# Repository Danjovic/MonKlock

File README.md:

# MonKlock

Cistercian Monk's cypher digital clock.
Resources
---------

- Project page at [hackaday](www.hackaday.com)

Features
--------

- Large (4 inch) 5x7 LED matrix
- Arduino Nano based
- DS3231 high precision RTC
- HH:MM or Decimal time
- Time, Day, Month and Year
- Single sided PCB

Contribute or Support
---------------------

If you are having issues, please email the athor [danjovic@hotmail.com](mailto:dnajovic@hotmail.com).

License
-------

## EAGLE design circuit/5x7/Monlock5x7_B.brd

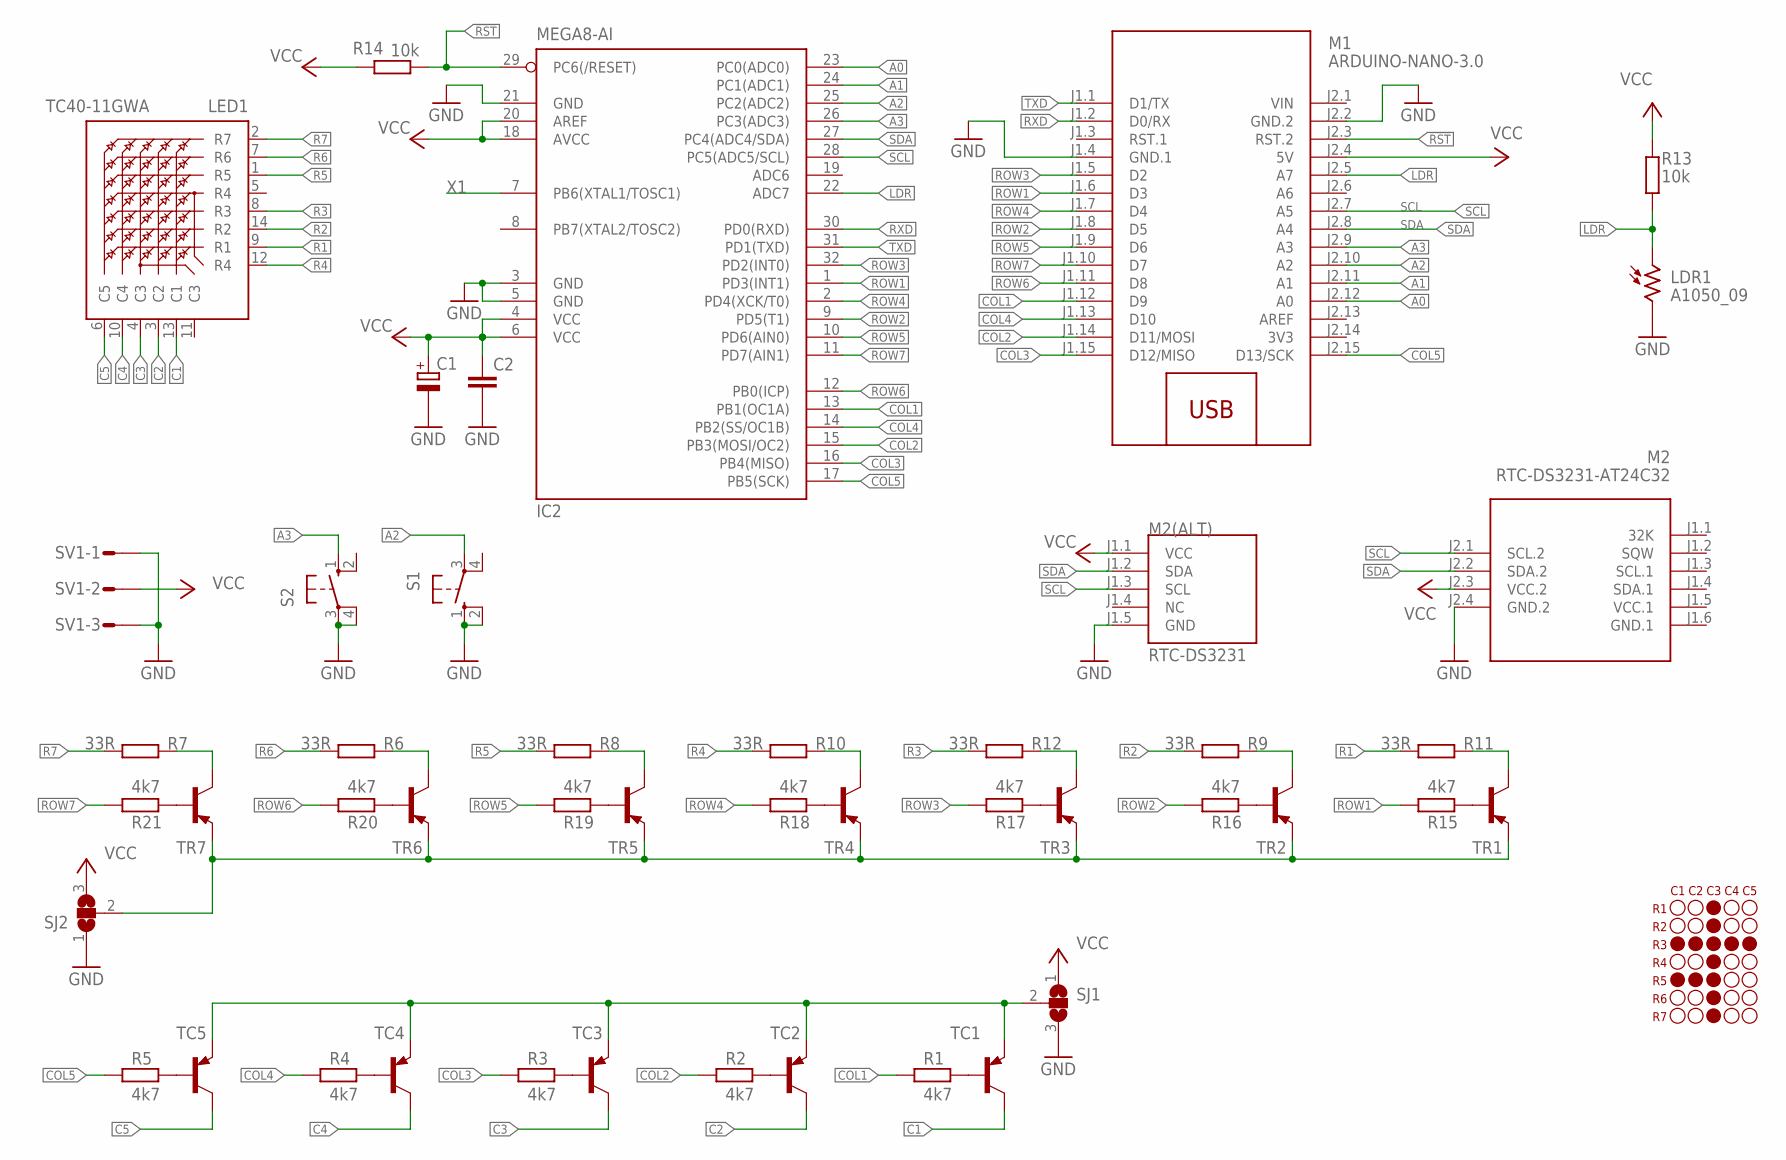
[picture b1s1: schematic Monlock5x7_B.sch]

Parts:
C1: CPOL-EU153CLV-0605; 153CLV-0605
C2: C-EUC0805K; C0805K
IC2: MEGA8-AI; TQFP32-08
LDR1: A1050_09; T0-46-A10XX
LED1: TC40-11GWA
M1: ARDUINO-NANO-3.0
M2: RTC-DS3231-AT24C32
M2(ALT): RTC-DS3231; RTC-DS3231_SMALL
R1, R2, R3, R4, R5, R15, R16, R17, R18, R19, R20, R21: 4k7; 0204/7
R6, R7, R8, R9, R10, R11, R12: 33R; 0204/7
R13: 10k; 0204/7
R14: 10k; M0805
S1, S2: 40-XX; B3F-40XX
SJ1, SJ2: SJ2W; SJ_2
SV1: S03P
TC1, TC2, TC3, TC4, TC5: BC327-PNP-TO92-EBC; TO92-EBC
TR1, TR2, TR3, TR4, TR5, TR6, TR7: BC327-PNP-TO92-EBC; TO92-EBC

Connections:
3V3: M1.J2.14 (3V3)
!RST: IC2.29 (PC6(/RESET)), M1.J2.3 (RST.2), R14.1
A0: IC2.23 (PC0(ADC0)), M1.J2.12 (A0)
A1: IC2.24 (PC1(ADC1)), M1.J2.11 (A1)
A2: IC2.25 (PC2(ADC2)), M1.J2.10 (A2), S1.3
A3: IC2.26 (PC3(ADC3)), M1.J2.9 (A3), S2.1 (S)
C1: LED1.13 (C1), TC1.C
C2: LED1.3 (C2), TC2.C
C3: LED1.4 (C3), TC3.C
C4: LED1.10 (C4), TC4.C
C5: LED1.6 (C5), TC5.C
CC1: R1.2, TC1.B
CC2: R2.2, TC2.B
CC3: R3.2, TC3.B
CC4: R4.2, TC4.B
CC5: R5.2, TC5.B
CC6: R15.2, TR1.B
COL1: IC2.13 (PB1(OC1A)), M1.J1.12 (D9), R1.1
COL2: IC2.15 (PB3(MOSI/OC2)), M1.J1.14 (D11/MOSI), R2.1
COL3: IC2.16 (PB4(MISO)), M1.J1.15 (D12/MISO), R3.1
COL4: IC2.14 (PB2(SS/OC1B)), M1.J1.13 (D10), R4.1
COL5: IC2.17 (PB5(SCK)), M1.J2.15 (D13/SCK), R5.1
GND: C1.-, C2.2, IC2.3 (GND), IC2.5 (GND), IC2.21 (GND), LDR1.2, M1.J1.4 (GND.1), M1.J2.2 (GND.2), M2.J2.4 (GND.2), M2(ALT).J1.5 (GND), S1.1 (S), S1.2 (S1), S2.3, S2.4 (P1), SJ1.3, SJ2.1, SV1.1, SV1.3
GND.1: M2.J1.6 (GND.1)
LDR: IC2.22 (ADC7), LDR1.1, M1.J2.5 (A7), R13.1
unnamed: SJ1.2, TC1.E, TC2.E, TC3.E, TC4.E, TC5.E
unnamed: SJ2.2, TR1.E, TR2.E, TR3.E, TR4.E, TR5.E, TR6.E, TR7.E
unnamed: R16.2, TR2.B
unnamed: R17.2, TR3.B
unnamed: R18.2, TR4.B
unnamed: R19.2, TR5.B
unnamed: R20.2, TR6.B
unnamed: R21.2, TR7.B
unnamed: R7.2, TR7.C
unnamed: R6.2, TR6.C
unnamed: R8.2, TR5.C
unnamed: R10.2, TR4.C
unnamed: R12.2, TR3.C
unnamed: R9.2, TR2.C
unnamed: R11.2, TR1.C
R1: LED1.9 (R1), R11.1
R2: LED1.14 (R2), R9.1
R3: LED1.8 (R3), R12.1
R4: LED1.12 (R4), R10.1
R5: LED1.1 (R5), R8.1
R6: LED1.7 (R6), R6.1
R7: LED1.2 (R7), R7.1
ROW1: IC2.1 (PD3(INT1)), M1.J1.6 (D3), R15.1
ROW2: IC2.9 (PD5(T1)), M1.J1.8 (D5), R16.1
ROW3: IC2.32 (PD2(INT0)), M1.J1.5 (D2), R17.1
ROW4: IC2.2 (PD4(XCK/T0)), M1.J1.7 (D4), R18.1
ROW5: IC2.10 (PD6(AIN0)), M1.J1.9 (D6), R19.1
ROW6: IC2.12 (PB0(ICP)), M1.J1.11 (D8), R20.1
ROW7: IC2.11 (PD7(AIN1)), M1.J1.10 (D7), R21.1
RXD: IC2.30 (PD0(RXD)), M1.J1.2 (D0/RX)
SCL: IC2.28 (PC5(ADC5/SCL)), M1.J2.7 (A5), M2.J2.1 (SCL.2), M2(ALT).J1.3 (SCL)
SDA: IC2.27 (PC4(ADC4/SDA)), M1.J2.8 (A4), M2.J2.2 (SDA.2), M2(ALT).J1.2 (SDA)
TXD: IC2.31 (PD1(TXD)), M1.J1.1 (D1/TX)
VCC: C1.+, C2.1, IC2.4 (VCC), IC2.6 (VCC), IC2.18 (AVCC), IC2.20 (AREF), M1.J2.4 (5V), M2.J2.3 (VCC.2), M2(ALT).J1.1 (VCC), R13.2, R14.2, SJ1.1, SJ2.3, SV1.2
VCC.1: M2.J1.5 (VCC.1)
VIN: M1.J2.1 (VIN)
X1: IC2.7 (PB6(XTAL1/TOSC1))

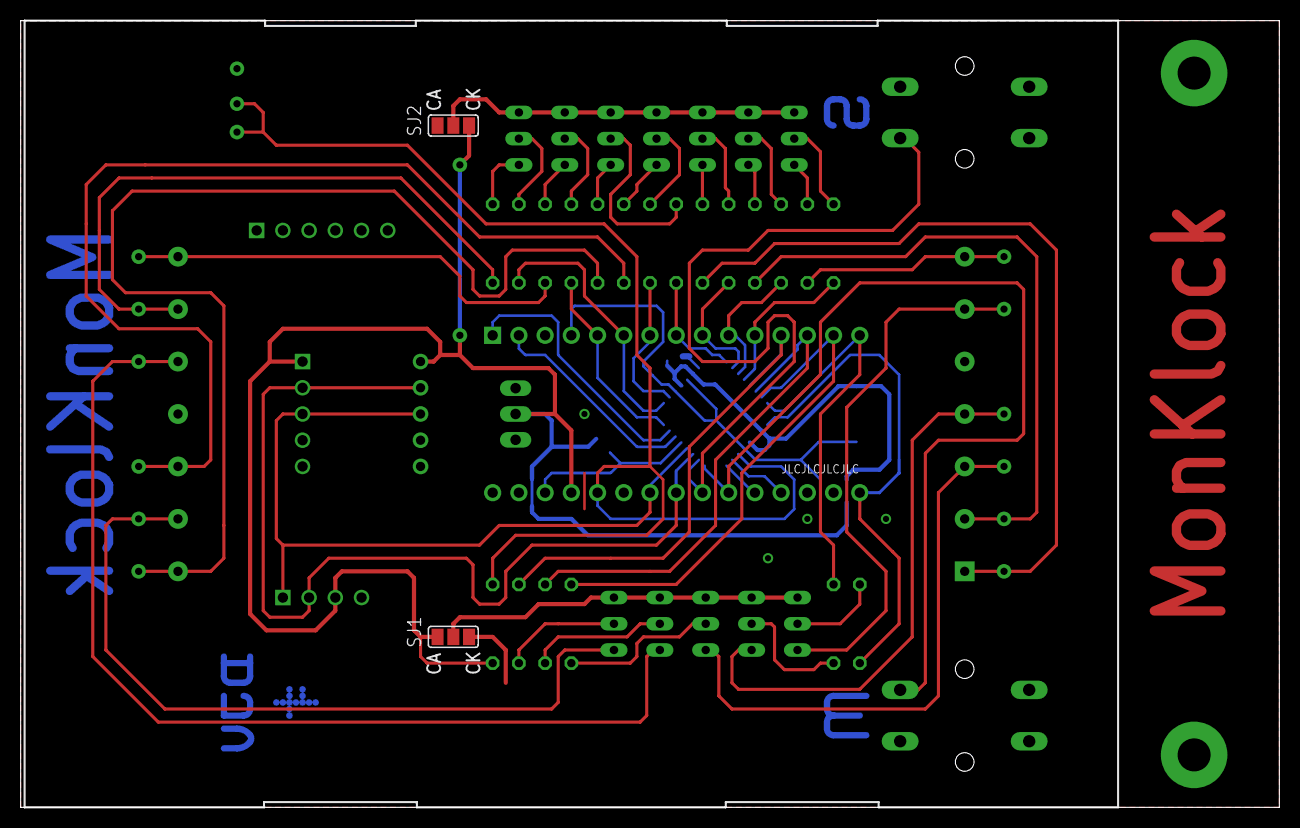
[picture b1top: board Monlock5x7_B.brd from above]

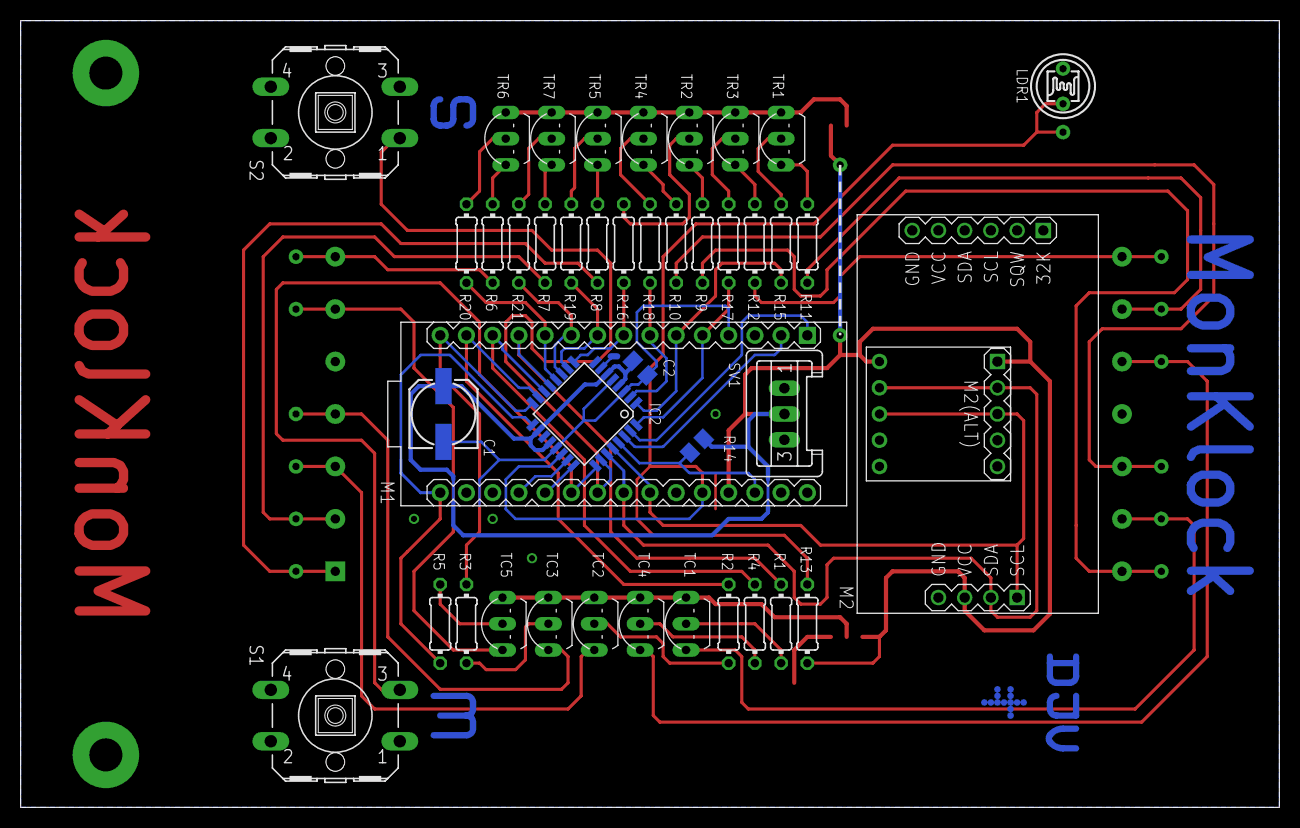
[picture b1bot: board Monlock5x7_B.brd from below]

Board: 2 copper layers, 121.9 x 76.2 mm, 46 parts (43 on the bottom side), 57 nets.

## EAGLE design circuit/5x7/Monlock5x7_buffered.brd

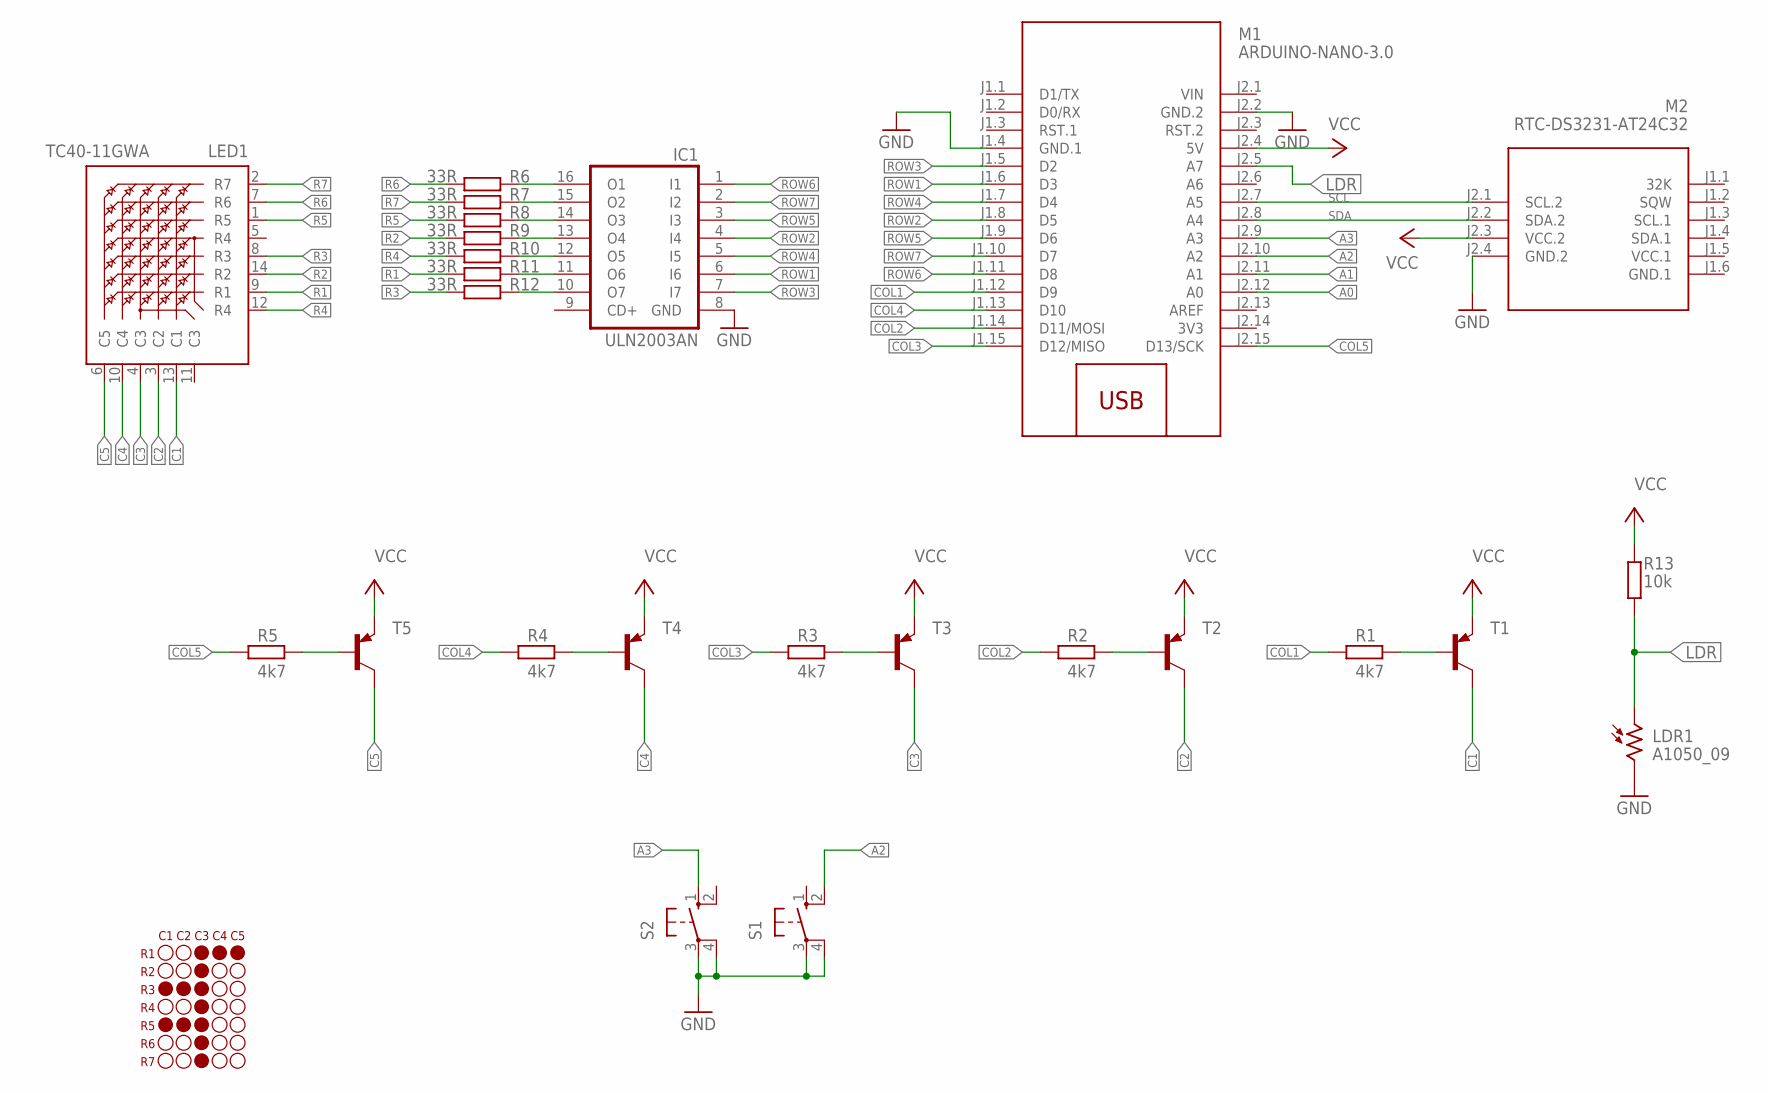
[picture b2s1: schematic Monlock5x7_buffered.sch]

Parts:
IC1: ULN2003AN; DIL16
LDR1: A1050_09; T0-46-A10XX
LED1: TC40-11GWA
M1: ARDUINO-NANO-3.0
M2: RTC-DS3231-AT24C32
R1, R2, R3, R4, R5: 4k7; 0204/7
R6, R7, R8, R9, R10, R11, R12: 33R; 0204/7
R13: 10k; 0204/7
S1, S2: 40-XX; B3F-40XX
T1, T2, T3, T4, T5: BC327-PNP-TO92-EBC; TO92-EBC

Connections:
3V3: M1.J2.14 (3V3)
A0: M1.J2.12 (A0)
A1: M1.J2.11 (A1)
A2: M1.J2.10 (A2), S1.2 (S1)
A3: M1.J2.9 (A3), S2.1 (S)
C1: LED1.13 (C1), T1.C
C2: LED1.3 (C2), T2.C
C3: LED1.4 (C3), T3.C
C4: LED1.10 (C4), T4.C
C5: LED1.6 (C5), T5.C
CC1: R1.2, T1.B
CC2: R2.2, T2.B
CC3: R3.2, T3.B
CC4: R4.2, T4.B
CC5: R5.2, T5.B
COL1: M1.J1.12 (D9), R1.1
COL2: M1.J1.14 (D11/MOSI), R2.1
COL3: M1.J1.15 (D12/MISO), R3.1
COL4: M1.J1.13 (D10), R4.1
COL5: M1.J2.15 (D13/SCK), R5.1
GND: IC1.8 (GND), LDR1.2, M1.J1.4 (GND.1), M1.J2.2 (GND.2), M2.J1.6 (GND.1), M2.J2.4 (GND.2), S1.3, S1.4 (P1), S2.3, S2.4 (P1)
LDR: LDR1.1, M1.J2.5 (A7), R13.1
unnamed: IC1.16 (O1), R6.2
unnamed: IC1.15 (O2), R7.2
unnamed: IC1.14 (O3), R8.2
unnamed: IC1.13 (O4), R9.2
unnamed: IC1.12 (O5), R10.2
unnamed: IC1.11 (O6), R11.2
unnamed: IC1.10 (O7), R12.2
R1: LED1.9 (R1), R11.1
R2: LED1.14 (R2), R9.1
R3: LED1.8 (R3), R12.1
R4: LED1.12 (R4), R10.1
R5: LED1.1 (R5), R8.1
R6: LED1.7 (R6), R6.1
R7: LED1.2 (R7), R7.1
ROW1: IC1.6 (I6), M1.J1.6 (D3)
ROW2: IC1.4 (I4), M1.J1.8 (D5)
ROW3: IC1.7 (I7), M1.J1.5 (D2)
ROW4: IC1.5 (I5), M1.J1.7 (D4)
ROW5: IC1.3 (I3), M1.J1.9 (D6)
ROW6: IC1.1 (I1), M1.J1.11 (D8)
ROW7: IC1.2 (I2), M1.J1.10 (D7)
SCL: M1.J2.7 (A5), M2.J2.1 (SCL.2)
SDA: M1.J2.8 (A4), M2.J2.2 (SDA.2)
VCC: M1.J2.4 (5V), M2.J2.3 (VCC.2), R13.2, T1.E, T2.E, T3.E, T4.E, T5.E
VCC.1: M2.J1.5 (VCC.1)
VIN: M1.J2.1 (VIN)

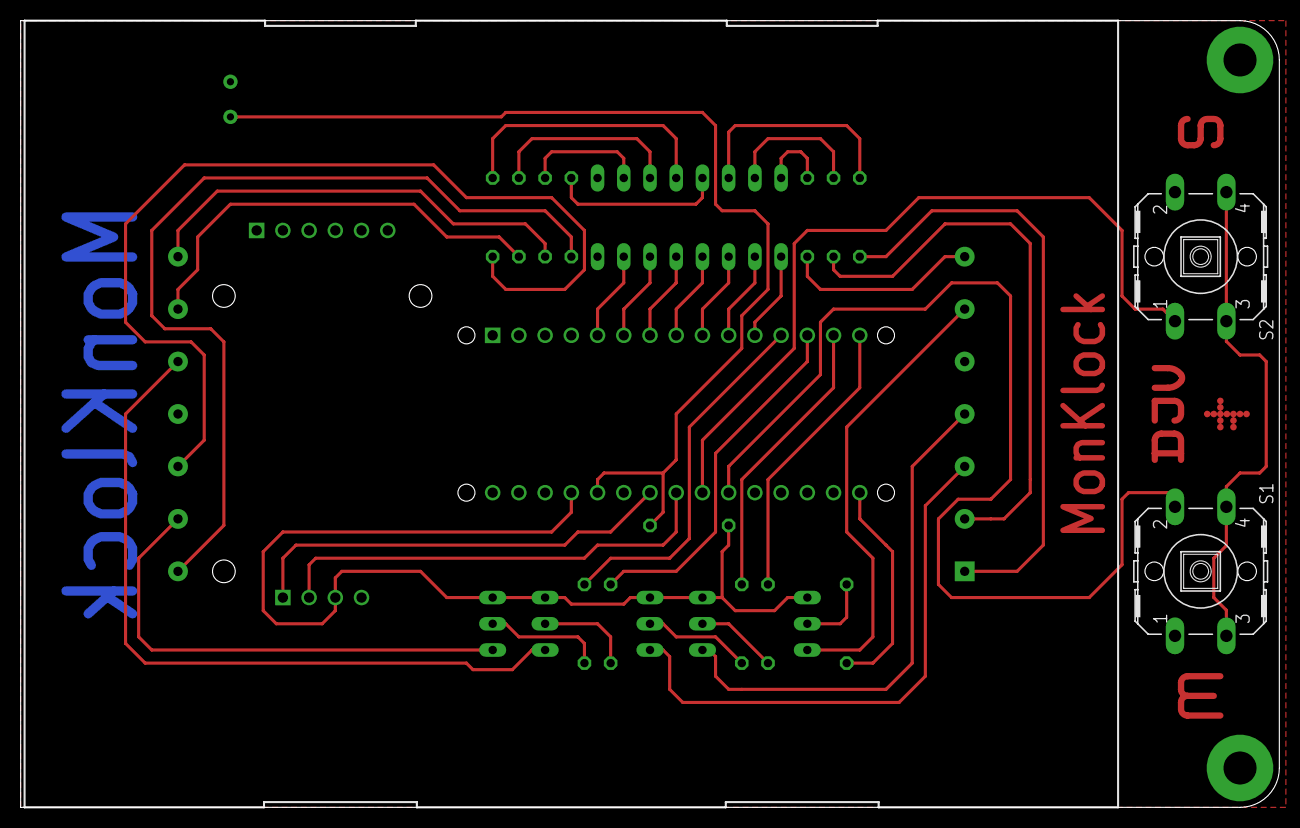
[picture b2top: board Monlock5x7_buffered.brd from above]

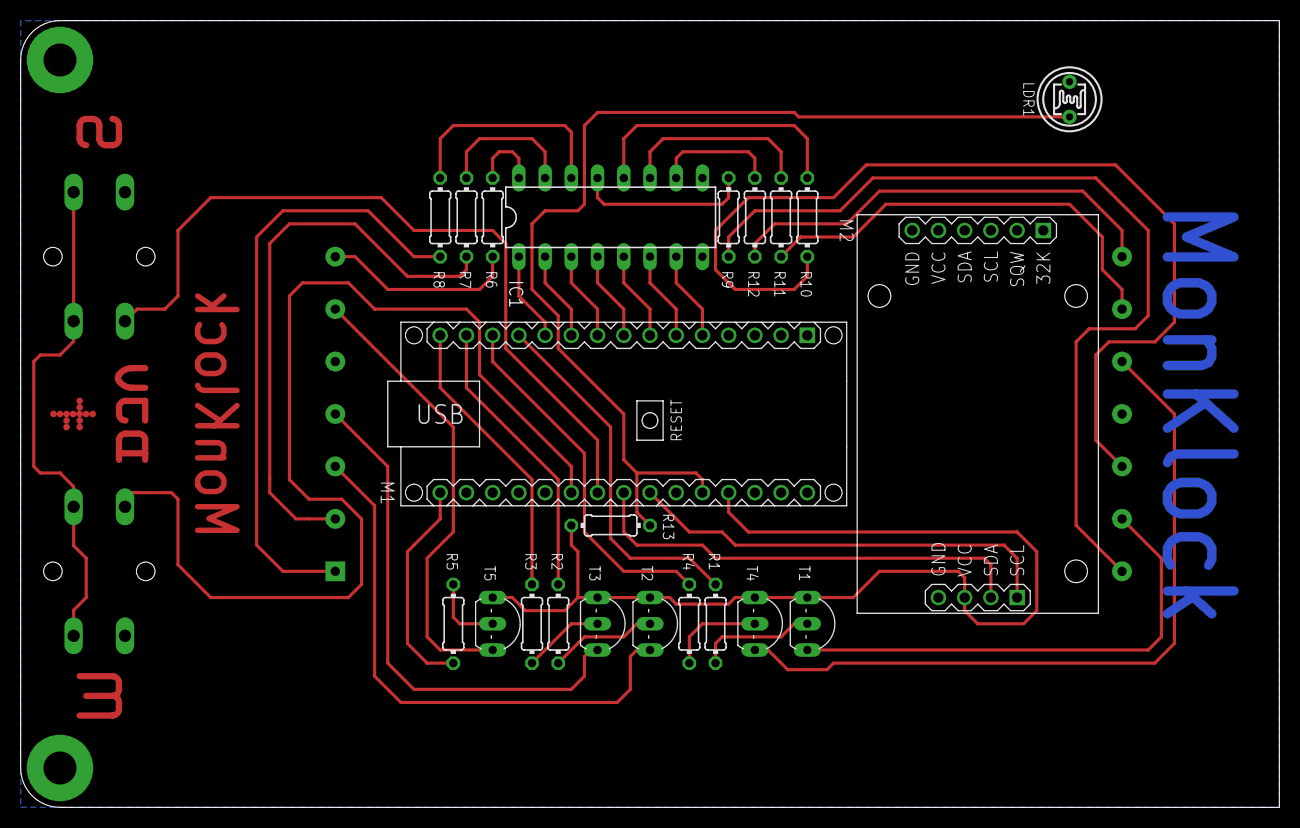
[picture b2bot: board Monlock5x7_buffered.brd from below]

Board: 2 copper layers, 121.9 x 76.2 mm, 25 parts (22 on the bottom side), 43 nets.

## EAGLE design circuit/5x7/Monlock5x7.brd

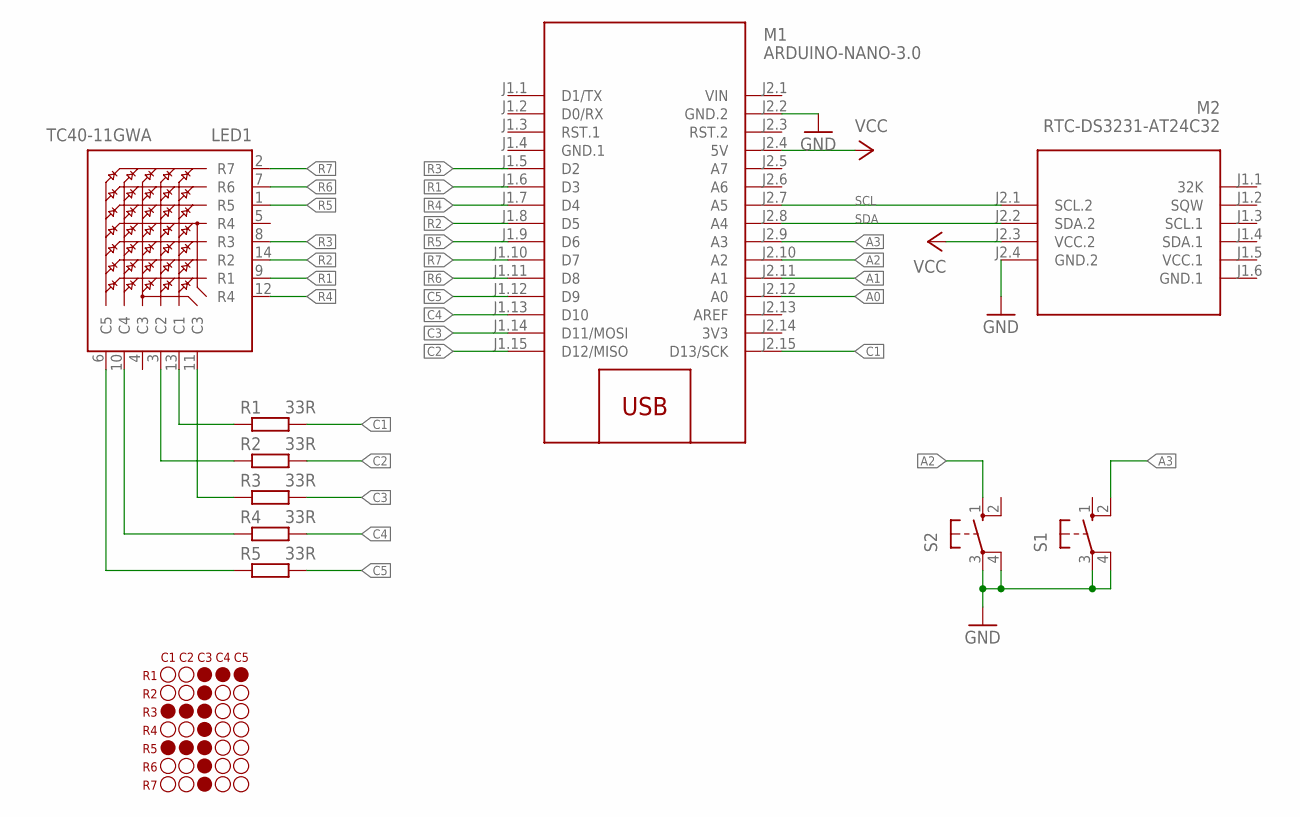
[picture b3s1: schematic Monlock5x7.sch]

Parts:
LED1: TC40-11GWA
M1: ARDUINO-NANO-3.0
M2: RTC-DS3231-AT24C32
R1, R2, R3, R4, R5: 33R; 0204/7
S1, S2: 40-XX; B3F-40XX

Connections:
3V3: M1.J2.14 (3V3)
A0: M1.J2.12 (A0)
A1: M1.J2.11 (A1)
A2: M1.J2.10 (A2), S2.1 (S)
A3: M1.J2.9 (A3), S1.2 (S1)
C1: M1.J2.15 (D13/SCK), R1.1
C2: M1.J1.15 (D12/MISO), R2.1
C3: M1.J1.14 (D11/MOSI), R3.1
C4: M1.J1.13 (D10), R4.1
C5: M1.J1.12 (D9), R5.1
CC1: LED1.13 (C1), R1.2
CC2: LED1.3 (C2), R2.2
CC3: LED1.11 (C3), R3.2
CC4: LED1.10 (C4), R4.2
CC5: LED1.6 (C5), R5.2
GND: M1.J1.4 (GND.1), M1.J2.2 (GND.2), M2.J1.6 (GND.1), M2.J2.4 (GND.2), S1.3, S1.4 (P1), S2.3, S2.4 (P1)
R1: LED1.9 (R1), M1.J1.6 (D3)
R2: LED1.14 (R2), M1.J1.8 (D5)
R3: LED1.8 (R3), M1.J1.5 (D2)
R4: LED1.12 (R4), M1.J1.7 (D4)
R5: LED1.1 (R5), M1.J1.9 (D6)
R6: LED1.7 (R6), M1.J1.11 (D8)
R7: LED1.2 (R7), M1.J1.10 (D7)
SCL: M1.J2.7 (A5), M2.J2.1 (SCL.2)
SDA: M1.J2.8 (A4), M2.J2.2 (SDA.2)
VCC: M1.J2.4 (5V), M2.J2.3 (VCC.2)
VCC.1: M2.J1.5 (VCC.1)
VIN: M1.J2.1 (VIN)

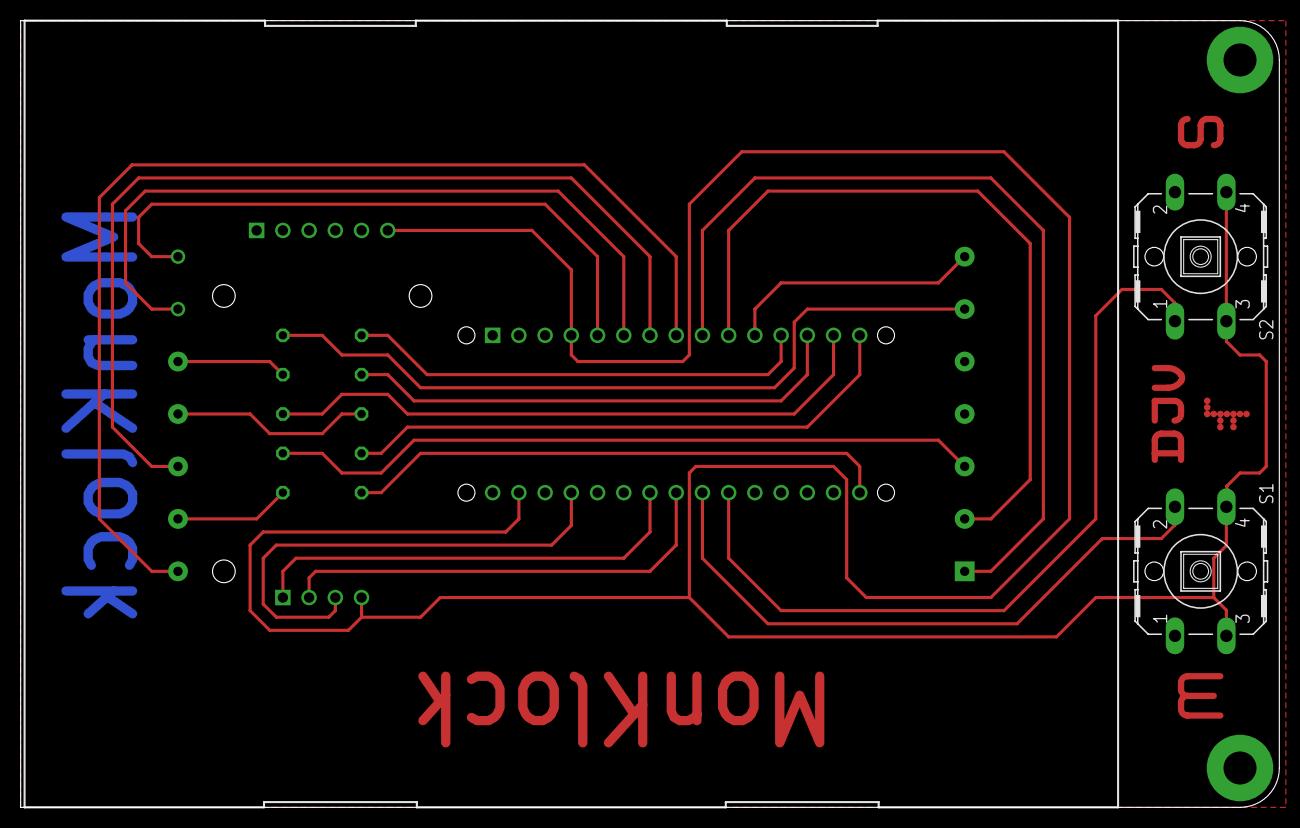
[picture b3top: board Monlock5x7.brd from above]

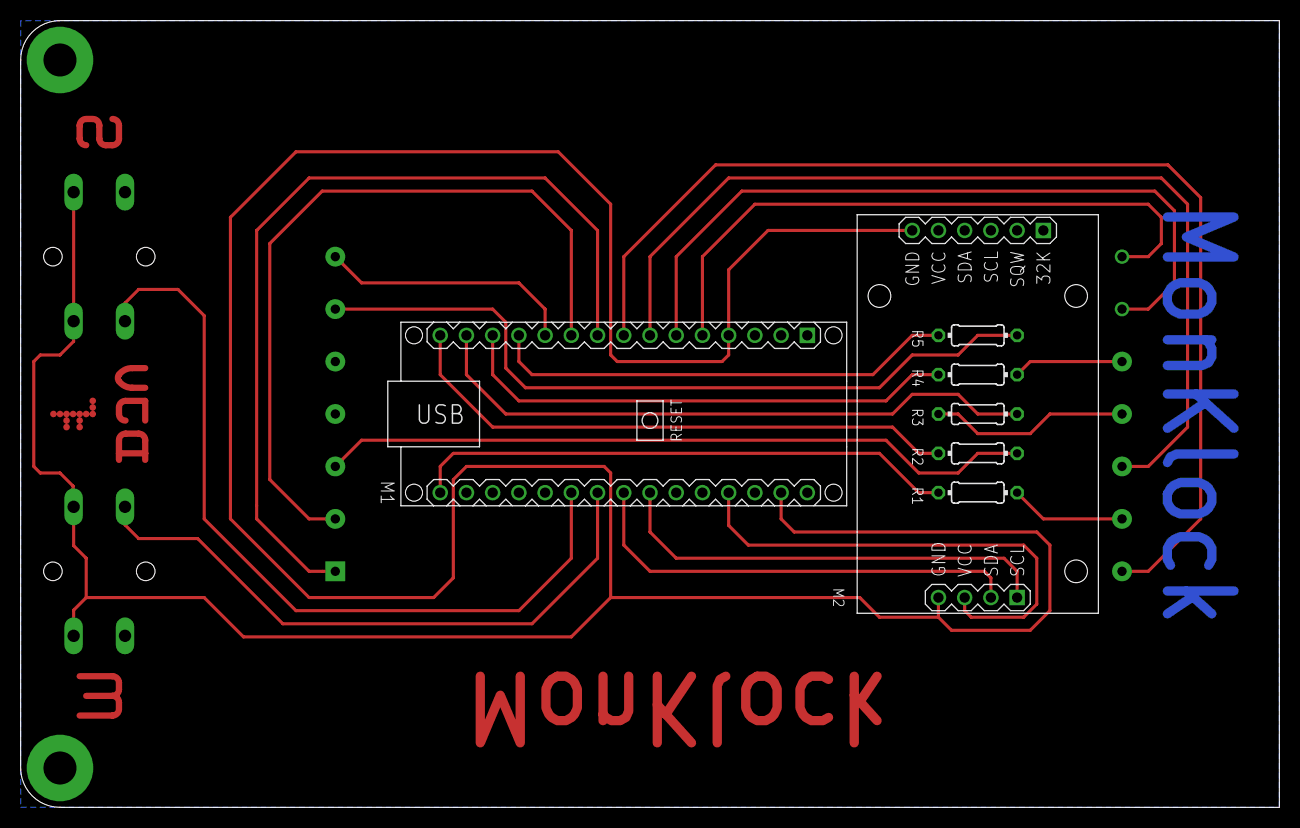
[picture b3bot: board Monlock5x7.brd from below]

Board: 2 copper layers, 121.9 x 76.2 mm, 10 parts (7 on the bottom side), 23 nets.

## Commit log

2021-03-07 Basic Release
2021-03-07 Working Version - HH:MM mode
2022-04-06 Buffered board (untested)
2022-09-16 New buffered version, use either CA or CK display

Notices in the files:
README.md:
[License: CC BY 4.0](http://creativecommons.org/licenses/by/4.0/)
parts and their libraries:
diy-modules: Released under the Creative Commons Attribution 4.0 International License: http://creativecommons.org/licenses/by/4.0
